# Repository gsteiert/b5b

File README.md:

# Beeping Blinking Banana plug NFC Test Battle Board

This is a board for testing the output power of different NFC I2C EEPROM

This also includes a WCH CH32V003 MCU to evaluate the feasibility of powering it from one of the NFC EEPROM.

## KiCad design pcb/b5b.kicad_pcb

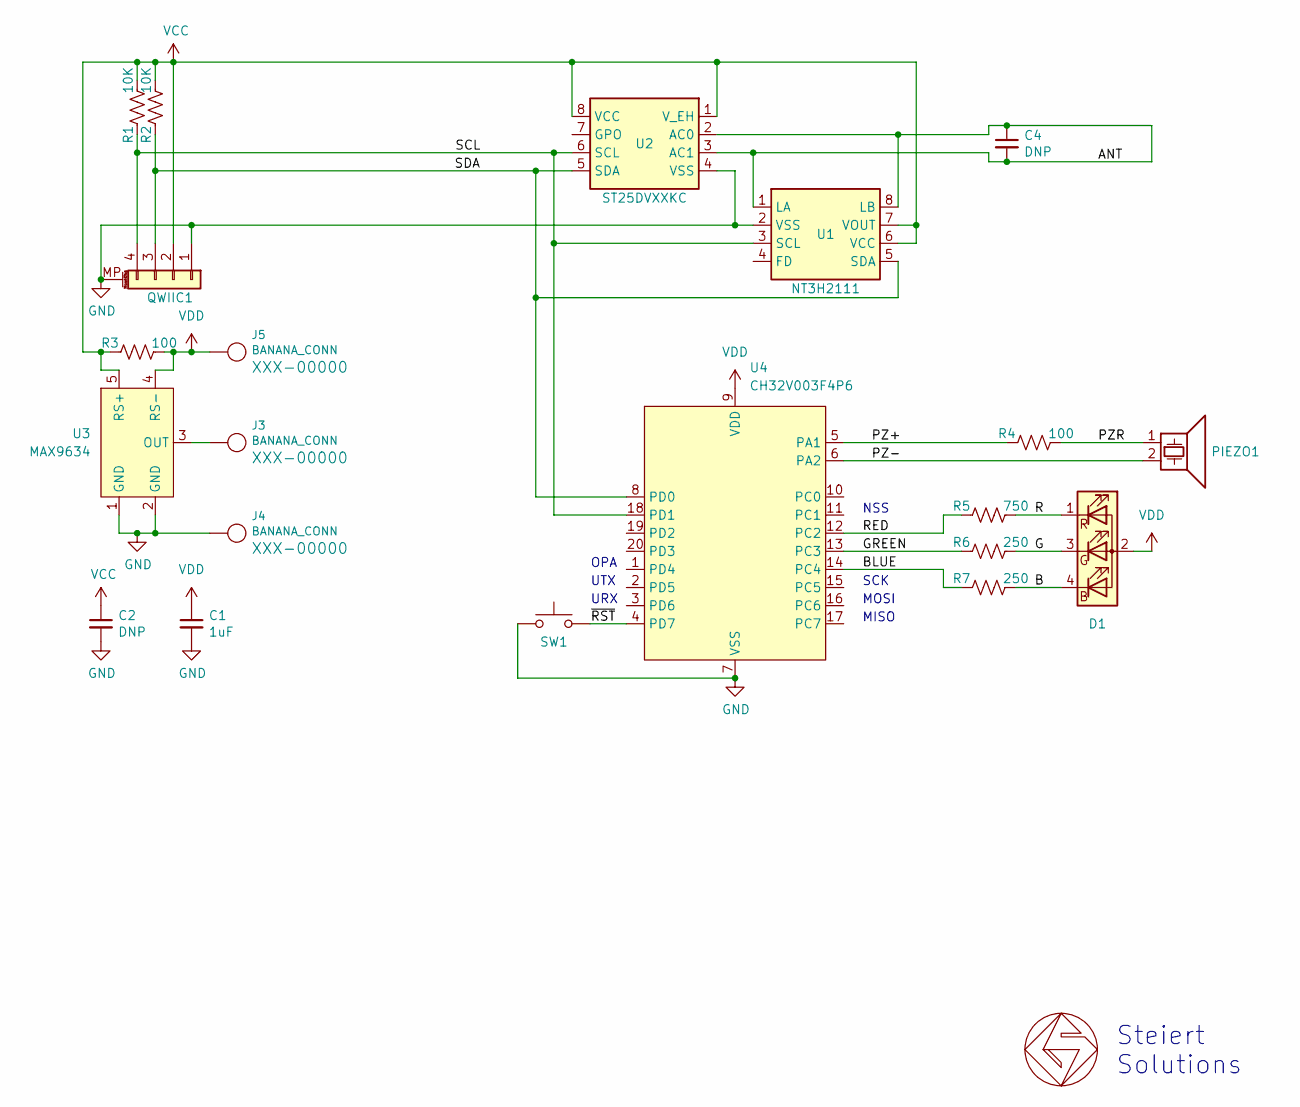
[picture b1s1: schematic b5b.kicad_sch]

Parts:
C1: 1uF; C_0603_1608Metric
C2: DNP; C_0603_1608Metric
C4: DNP; C_0402_1005Metric
D1: LED_RAGB; LED_Kingbright_AAA3528ESGCT
GS1: GS_logo; gs_logo_200mil
J3, J4, J5: BANANA_CONN; banana
PIEZO1: Speaker_Crystal; Buzzer_Murata_PKMCS0909E4000-R1
QWIIC1: Conn_01x04_MountingPin; JST_SH_SM04B-SRSS-TB_1x04-1MP_P1.00mm_Horizontal
R1, R2: 10K; R_0603_1608Metric
R3, R4: 100; R_0603_1608Metric
R5: 750; R_0603_1608Metric
R6, R7: 250; R_0603_1608Metric
SW1: SW_Push; SW_Push_1P1T_NO_Vertical_Wuerth_434133025816
U1: NT3H2111; SO-8_3.9x4.9mm_P1.27mm
U2: ST25DVXXKC; SO-8_3.9x4.9mm_P1.27mm
U3: MAX9634; SOT-23-5
U4: CH32V003F4P6; TSSOP-20_4.4x6.5mm_P0.65mm

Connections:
/ANT: C4.1, C4.2, U1.1 (LA), U1.8 (LB), U2.2 (AC0), U2.3 (AC1)
/B: D1.4 (BK), R7.1
/BLUE: R7.2, U4.14 (PC4)
/G: D1.3 (GK), R6.1
/GREEN: R6.2, U4.13 (PC3)
/PZ+: R4.2, U4.5 (PA1)
/PZ-: PIEZO1.2, U4.6 (PA2)
/PZR: PIEZO1.1, R4.1
/R: D1.1 (RK), R5.1
/RED: R5.2, U4.12 (PC2)
/SCL: QWIIC1.4, R1.2, U1.3 (SCL), U2.6 (SCL), U4.18 (PD1)
/SDA: QWIIC1.3, R2.2, U1.5 (SDA), U2.5 (SDA), U4.8 (PD0)
/~RST: SW1.2, U4.4 (PD7)
GND: C1.2, C2.2, J4.1, QWIIC1.1, QWIIC1.MP (MountPin), SW1.1, U1.2 (VSS), U2.4 (VSS), U3.1 (GND), U3.2 (GND), U4.7 (VSS)
unnamed: J3.1, U3.3 (OUT)
VCC: C2.1, QWIIC1.2, R1.1, R2.1, R3.2, U1.6 (VCC), U1.7 (VOUT), U2.1 (V_EH), U2.8 (VCC), U3.5 (RS+)
VDD: C1.1, D1.2 (A), J5.1, R3.1, U3.4 (RS-), U4.9 (VDD)

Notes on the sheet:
Steiert Solutions
MISO
SCK
UTX
OPA
URX
NSS
MOSI

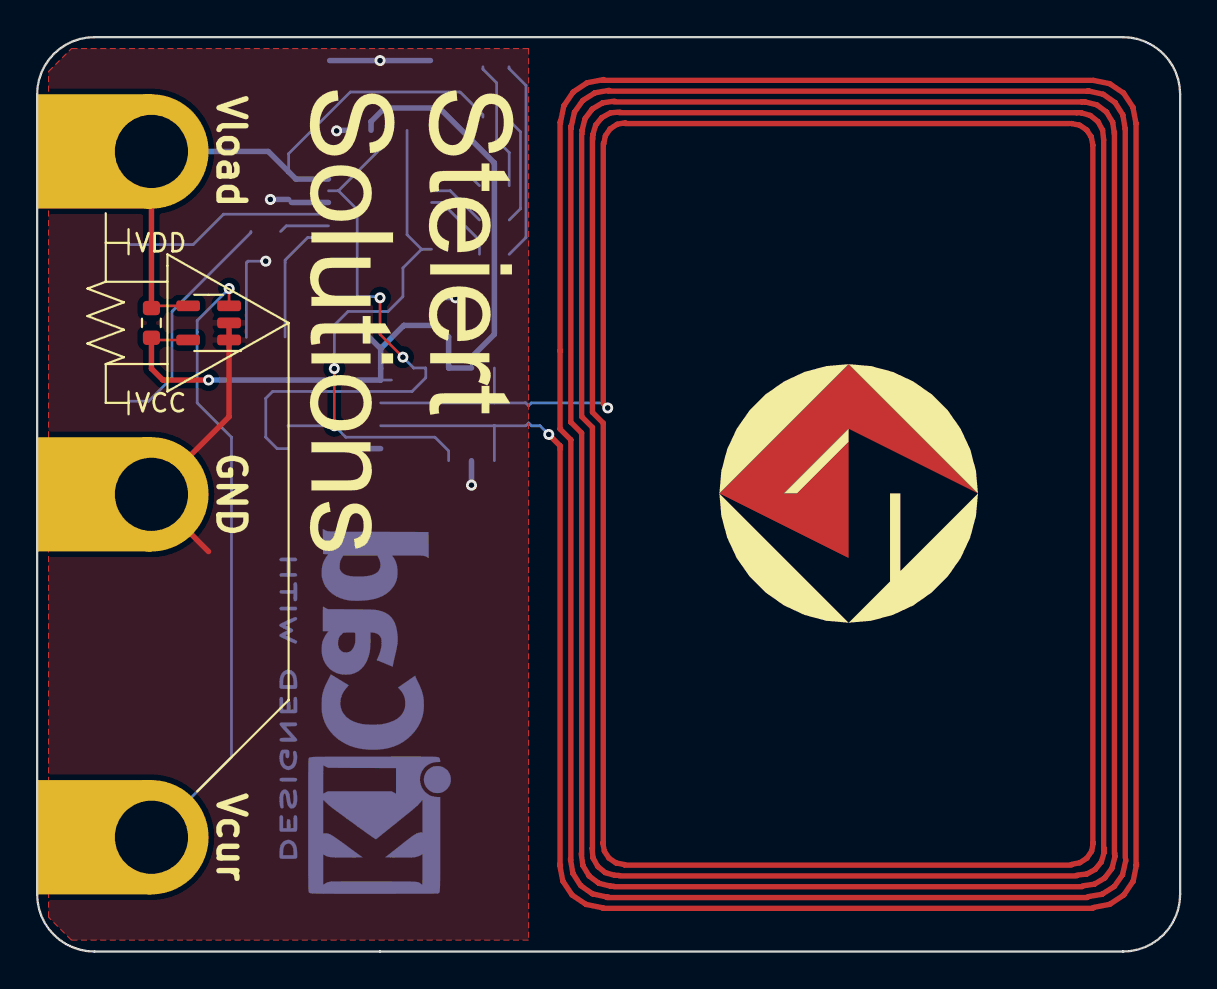
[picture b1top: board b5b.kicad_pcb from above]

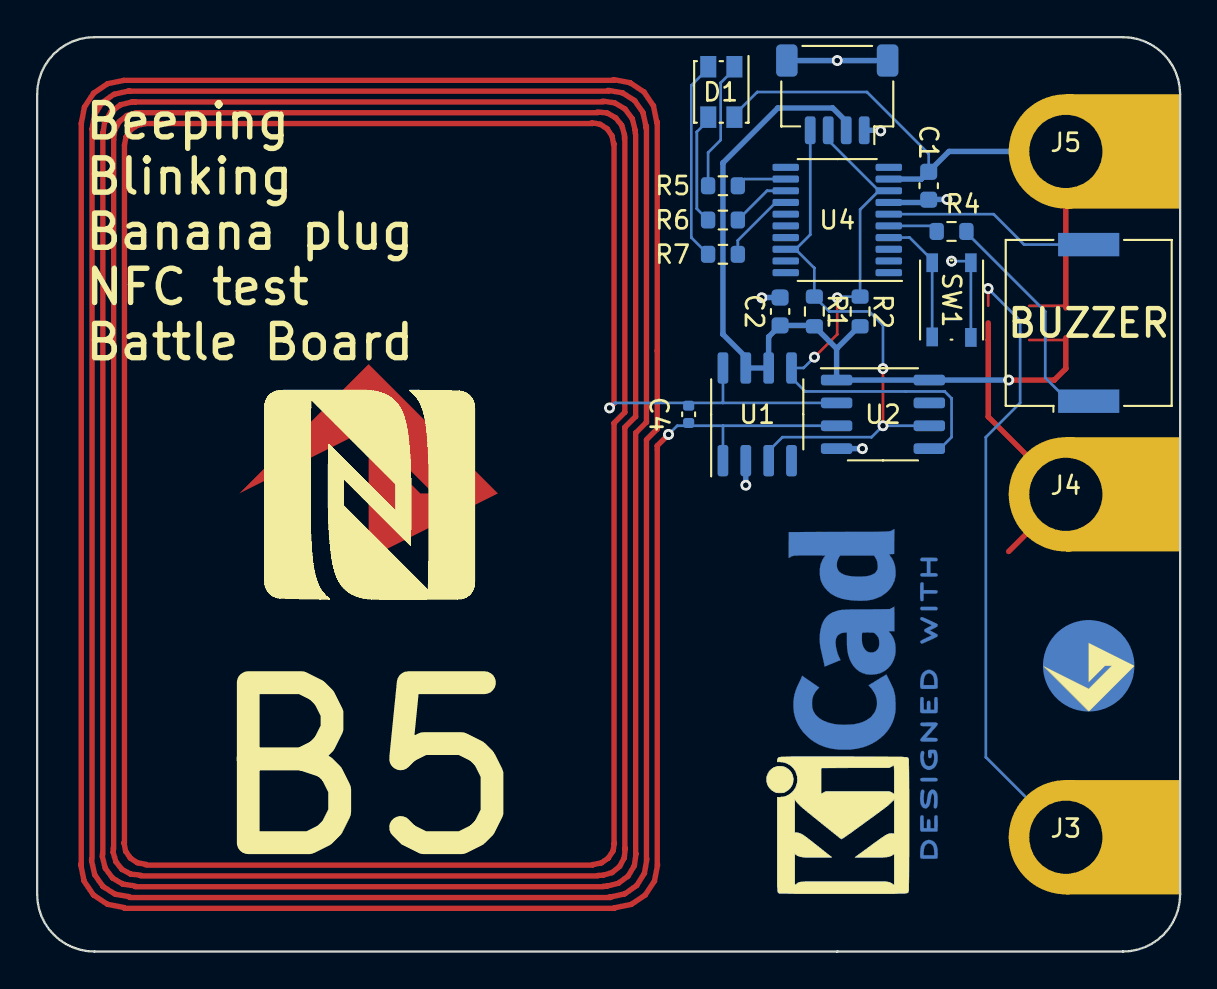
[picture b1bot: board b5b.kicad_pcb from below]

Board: 2 copper layers, 63.5 x 50.8 mm, 22 parts (20 on the bottom side), 17 nets.

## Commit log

2024-05-12 checking in completed NFC Test board
